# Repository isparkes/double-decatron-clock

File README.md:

# Two Decatron Clock

KiCad hardware for a two-tube Decatron (dekatron) clock driven by a Wemos D1 Mini
(ESP8266), plus the tube carrier board and an early, unfinished firmware sketch.

The board generates its own ~400 V anode supply and ~110 V guide rail, drives two
dual-guide A101 dekatrons, and reads each tube's index mark back through an
optocoupler.

> ⚠️ **This board carries ~400 V DC.** The HV multiplier and the tube connectors are
> live whenever `HV_EN` is asserted, and the reservoir capacitors stay charged after
> power-off. Treat the whole top side as hot.

## Status

The hardware is finished and was fabricated (`adfed9c Fab`, Oct 2021), with small
fixes through to Dec 2023.

**The standalone firmware was never finished.** The sketch under `Software/` stops
at version 0.1: it brings up Wi-Fi, NTP, the DS1307 and the full web config UI, and
it can step each tube, but there is no timer ISR and nothing ever renders the
prepared `displayHours` / `displayMins` / `displaySecs` values onto the tubes. The
only stepping that happens is the manual, button-driven index hunt in `setup()`.
Its pin map in `Software/ClockDefs.h` also predates commit `835bd50` ("Rearrange
outputs so that IDX work correctly") and **does not match the board as fabricated** —
see the pin table below for the as-built mapping.

Instead of being finished as a standalone clock, the board was repurposed as the
**dual-Decatron seconds display add-on for the ENIAC nixie clock**. The firmware it
actually runs lives in the separate `eniac-firmware` repository, as
`EniacDecatron` — an ESP8266 slave that receives a 5-byte framed packet
(`0xAA`, hours, minutes, seconds, control) once per second over UART from the ENIAC
ESP32 master, homes both tubes against their index marks, and drives tube 1 as a
rotating seconds hand. `DecatronTest` in the same repository emulates the master for
bench testing.

Because the add-on takes its time over the serial link, the on-board DS1307, the
Wi-Fi stack and the web UI are all unused in that role. Note that the front-panel
connector's `BTN1` pin lands on the Wemos `RX` pin — in ENIAC use that pin carries
serial data from the master instead of a button.

`Software/DecatronClock/` is a newer attempt at the standalone case: a PlatformIO
project built on the EniacDecatron tube handling, with the UART link to the ENIAC
master replaced by a local time source (NTP → DS1307 → serial), showing hours on one
tube and minutes on the other. It is a working skeleton rather than a finished
clock — see [`Software/DecatronClock/README.md`](Software/DecatronClock/README.md).

## Repository layout

| Path | Description |
|---|---|
| `Hardware/` | Main board: Wemos D1 Mini carrier, HV supply, guide drivers, index sensing, RTC. KiCad project `WemosDecatron`. |
| `Hardware/A101base/` | Dual A101 tube carrier board. KiCad project `A101base`. |
| `Hardware/WemosDecatronExternal.sch` | Off-board front-panel sheet (button + PIR). Legacy KiCad 4 schematic, documentation only — no PCB, and it still shows an 8-way front connector where the main board now has a 5-way one. Rendered as `WemosDecatronExternal.svg`. |
| `Hardware/Recovered.pretty/` | Recovered footprints. |
| `LICENSE` | Attribution / non-commercial terms covering both the hardware and the firmware. |
| `Software/DecatronClock/` | Standalone clock firmware: hours on one tube, minutes on the other. PlatformIO, ESP8266. |
| `Software/*.ino`, `Software/*.cpp` | Abandoned v0.1 standalone firmware (Arduino IDE, ESP8266). Reference only. |

Gerbers and drill files for `A101base` are generated into `A101base/CAM/`, which is
git-ignored along with the KiCad `*-backups` directories.

## Hardware

### Main board — `Hardware/WemosDecatron`

65 × 75 mm, two layers, through-hole throughout, four M3 mounting holes.
Title block: *"Wemos D1 Two Decatron clock"*, Rev 002, Glowtime Ltd.

**Power in.** DC enters on `J3`, through reverse-polarity diode `D1` (UF4007) to
`VIN`, then an L7805 (`U3`) produces the 5 V `VCC` that feeds the Wemos.

**High voltage.** An MC34063A (`U4`) switches an IRF640 (`Q2`) through a 100 µH
inductor (`L1`), with `R1` (0R18 2 W) as the current sense. `D3` rectifies the
switch node into the ~150 V rail (`C13` reservoir). A three-stage
Cockcroft–Walton multiplier (`C1`–`C4`, `D4`–`D7`) hanging off the same switch node
produces the ~400 V anode rail. Feedback is set by `R4`/`R5`/`RV1`; `RV1` (1 k) trims
the output.

**HV enable.** `Q5` (2N7000), driven from `HV_EN`, switches the feedback divider so
the firmware can turn the generator off for blanking. Solder jumper `JP1` ties
`HV_EN` to `VCC` for bench bring-up without a microcontroller.

**Tube drive.** Each tube's anode is fed from the 400 V rail through a 470 k series
resistor (`R16` for tube 1, `R2` for tube 2). `R12` (33 k) drops the 150 V rail to
the ~110 V guide rail. Each guide sits at 110 V through a 470 k pull-up
(`R9`/`R11` for tube 1, `R18`/`R20` for tube 2) and is pulled to ground by an MPSA42
(`Q3`/`Q4` and `Q6`/`Q7`). The common cathode return `RTN` is decoupled by `C5` and
`C15` (added in `021e908`, "Add RTN smoothing caps").

**Index sensing.** The index cathode of each tube drives the LED of an EL817
optocoupler (`U1`, `U6`) against `RTN`; the transistor side pulls `IDX1`/`IDX2` down
against a 3V3 pull-up (`R15`, `R21`). The index signal is therefore **active low** and
fully isolated from the HV side.

**Timekeeping.** A DS1307 (`U5`) with crystal `Y1` and CR1220 backup cell `BT1`,
on the Wemos I²C pins, also brought out on the 4-way header `J5` (added in
`6aa0615`).

**Test pads.** `W1` 5V, `W2`/`W3` GND, `W4` the 150 V rail (silk reads 170 V),
`W5` 110 V, `W6` `RTN` (silk reads 55 V), `W7` 400 V, `W8` `VIN`.

### Tube carrier — `Hardware/A101base`

71 × 39 mm, two layers. Two A101 dekatron footprints (`D1`, `D2`), each with its own
5-way header, plus two M3 mounting holes. Title block: *"A101 tube mount"*, Rev 001.

Per tube it commons K0 and K2–K9 to the return pin and brings out the anode, the
**K1 index cathode**, and the two guides. Note that the index is taken from K1, not
K0.

## Connectors

### Main board

| Ref | Pins | Function | Pinout |
|---|---|---|---|
| `J1` | 5 | Decatron 1 | 1 `400V_1` · 2 `IDX_IN1` · 3 `RTN` · 4 `G2_1` · 5 `G1_1` |
| `J4` | 5 | Decatron 2 | 1 `400V_2` · 2 `IDX_IN2` · 3 `RTN` · 4 `G2_2` · 5 `G1_2` |
| `J2` | 5 | Front panel | 1 `GND` · 2 `BTN1` · 3 `PIR` · 4 `VCC` (5 V) · 5 `3V3` |
| `J3` | 2 | DC input | 1 `GND` · 2 `V+` |
| `J5` | 4 | I²C | 1 `SDA` · 2 `SCL` · 3 `3V3` · 4 `GND` |

### A101 carrier (`J1`, `J2`)

| Pin | Signal |
|---|---|
| 1 | Anode |
| 2 | K1 (index) |
| 3 | Common return (K0, K2–K9) |
| 4 | G1 |
| 5 | G2 |

**Guide ordering:** with a straight 1:1 cable, main-board pin 4 (`G2_n`) lands on the
carrier's `G1` and pin 5 (`G1_n`) on `G2`, so the guide pair is swapped and the glow
rotates the opposite way round. The firmware compensates in its phase sequence —
`EniacDecatron` steps the glow *forward* by *decrementing* the phase. Keep this in
mind before "fixing" either end.

## ESP8266 pin map (as fabricated)

Taken from the PCB netlist, not from `Software/ClockDefs.h`.

`EniacDecatron` and `Software/DecatronClock` use the same set of pins, but their
`defs.h` deliberately maps them differently: firmware "Decatron 1" is the board's
`J4`/Decatron2 connector, and G1/G2 are swapped within each tube, to compensate for
the pin 4/5 ordering described above. That mapping is empirical and known to work —
do not reconcile it with this table without a tube on the bench. (The
`EniacDecatron/SPECIFICATION.md` pin table is itself out of date with respect to its
own `defs.h`.)

| Signal | D1 Mini pin | Direction | Notes |
|---|---|---|---|
| `G1_1` | D4 | out | Tube 1 guide 1 |
| `G2_1` | D3 | out | Tube 1 guide 2 |
| `IDX1` | D0 | in | Tube 1 index, active low (opto) |
| `G1_2` | D6 | out | Tube 2 guide 1 |
| `G2_2` | D5 | out | Tube 2 guide 2 |
| `IDX2` | D7 | in | Tube 2 index, active low (opto) |
| `HV_EN` | D8 | out | HV generator enable, active high |
| `SDA` | D2 | — | DS1307 / `J5` |
| `SCL` | D1 | — | DS1307 / `J5` |
| `PIR` | A0 | in | Front panel `J2` |
| `BTN1` | RX | in | Front panel `J2`; also the UART RX used by `EniacDecatron` |

## Working with the files

The schematics are KiCad 6 format (`version 20211123`); `WemosDecatron.kicad_pcb` has
since been re-saved by a newer KiCad and will want to migrate the schematic on open.
The legacy KiCad 5 files (`.sch`, `.net`, `.lib`, `.cmp`, `.mod`) are kept alongside
for reference and are not maintained.

Footprints come from a global `NixieClockMaster` library that is **not** part of this
repository; the local `fp-lib-table` is empty, so that library must be configured
globally in KiCad for the boards to open with footprints resolved.
`Hardware/WemosDecatron.csv` is a BOM export, generated before the latest revisions —
check it against the schematic before ordering.

### Firmware

For a standalone clock, build `Software/DecatronClock` with PlatformIO
(`pio run -t upload`, env `d1_mini`). No external library dependencies.

For the add-on role, build `EniacDecatron` from the `eniac-firmware` repository, also
with PlatformIO (env `d1_mini`, 160 MHz, 115200 baud).

The loose sketch at the top of `Software/` is an Arduino IDE project (board:
*LOLIN(WeMos) D1 R2 & mini*, 4 MB flash / 2 MB FS). It depends on Time (Margolis
1.5.0) and WiFiManager (tzapu 0.14.0). It is kept for reference only — it is
incomplete and its pin map is out of date.

## License

Attribution-NonCommercial — see [`LICENSE`](LICENSE). Free to use, modify and build
for personal, educational and hobbyist purposes, with credit; commercial use,
including selling boards or kits, needs a separate written license. The same terms
as the `eniac-firmware` repository.

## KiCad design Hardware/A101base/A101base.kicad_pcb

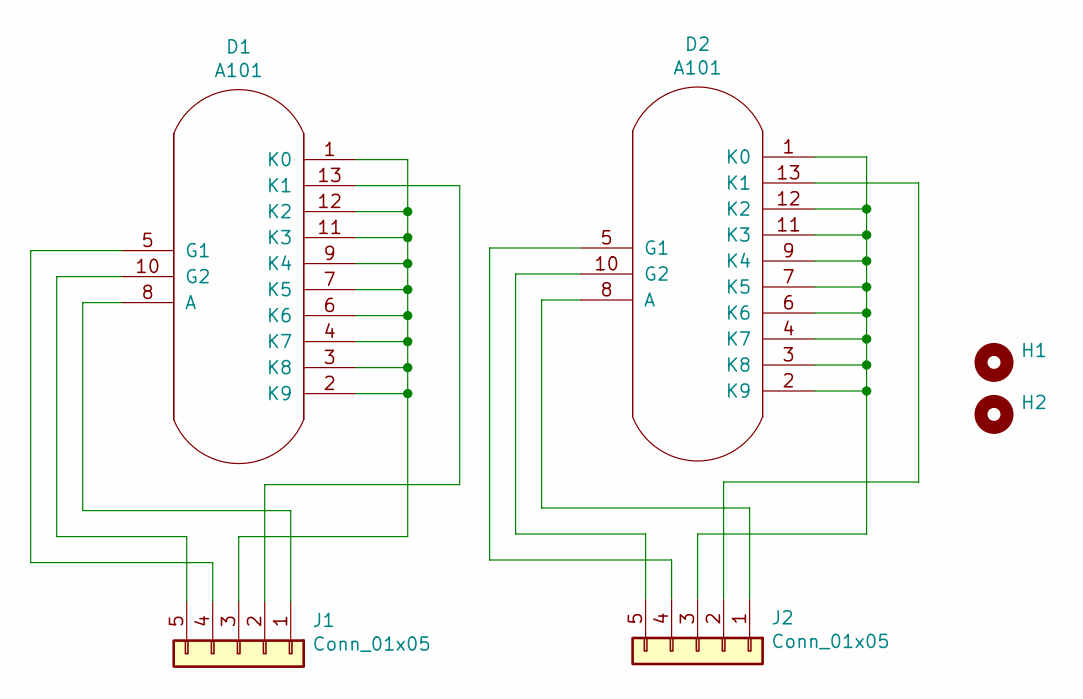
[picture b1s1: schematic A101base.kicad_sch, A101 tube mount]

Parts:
D1, D2: A101; A101-TopView
H1, H2: MountingHole; MountingHole_3.2mm_M3
J1, J2: Conn_01x05; Header_MA05-1

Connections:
unnamed: D1.1 (K0), D1.2 (K9), D1.3 (K8), D1.4 (K7), D1.6 (K6), D1.7 (K5), D1.9 (K4), D1.11 (K3), D1.12 (K2), J1.3
unnamed: D1.5 (G1), J1.4
unnamed: D1.8 (A), J1.1
unnamed: D1.10 (G2), J1.5
unnamed: D1.13 (K1), J1.2
unnamed: D2.1 (K0), D2.2 (K9), D2.3 (K8), D2.4 (K7), D2.6 (K6), D2.7 (K5), D2.9 (K4), D2.11 (K3), D2.12 (K2), J2.3
unnamed: D2.5 (G1), J2.4
unnamed: D2.8 (A), J2.1
unnamed: D2.10 (G2), J2.5
unnamed: D2.13 (K1), J2.2

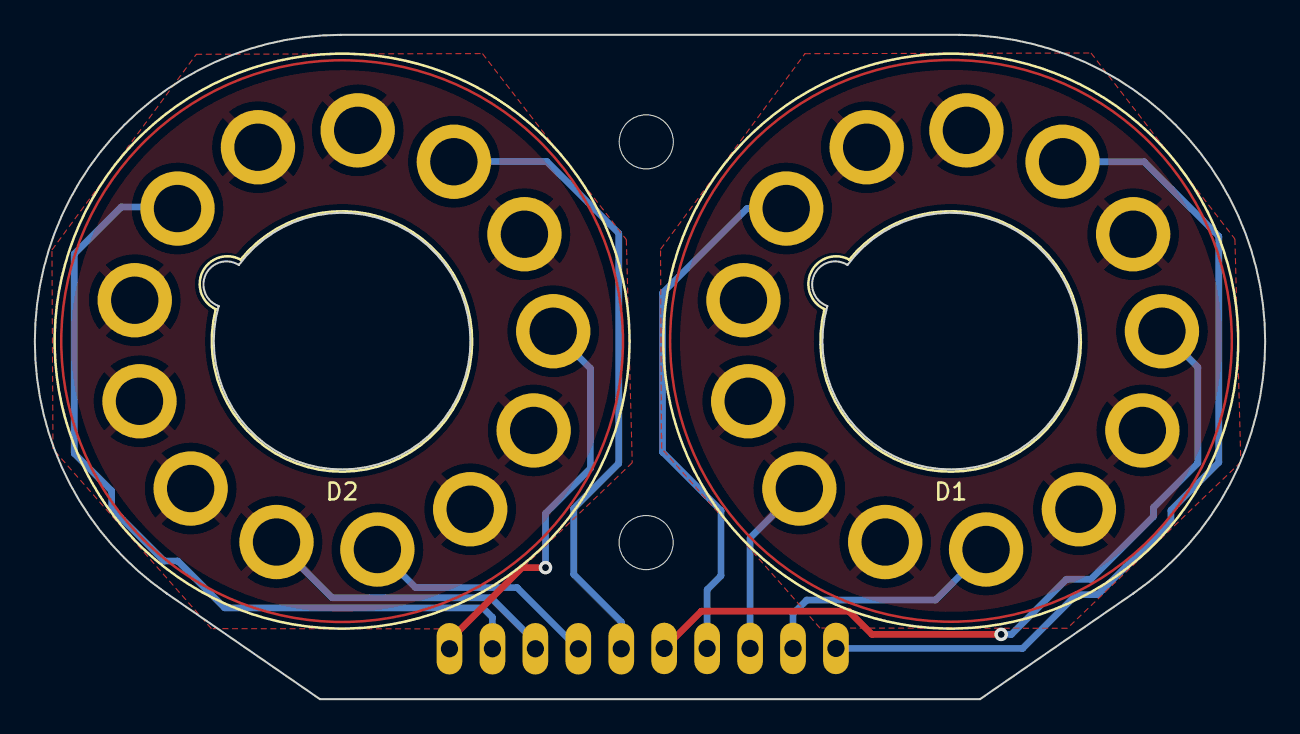
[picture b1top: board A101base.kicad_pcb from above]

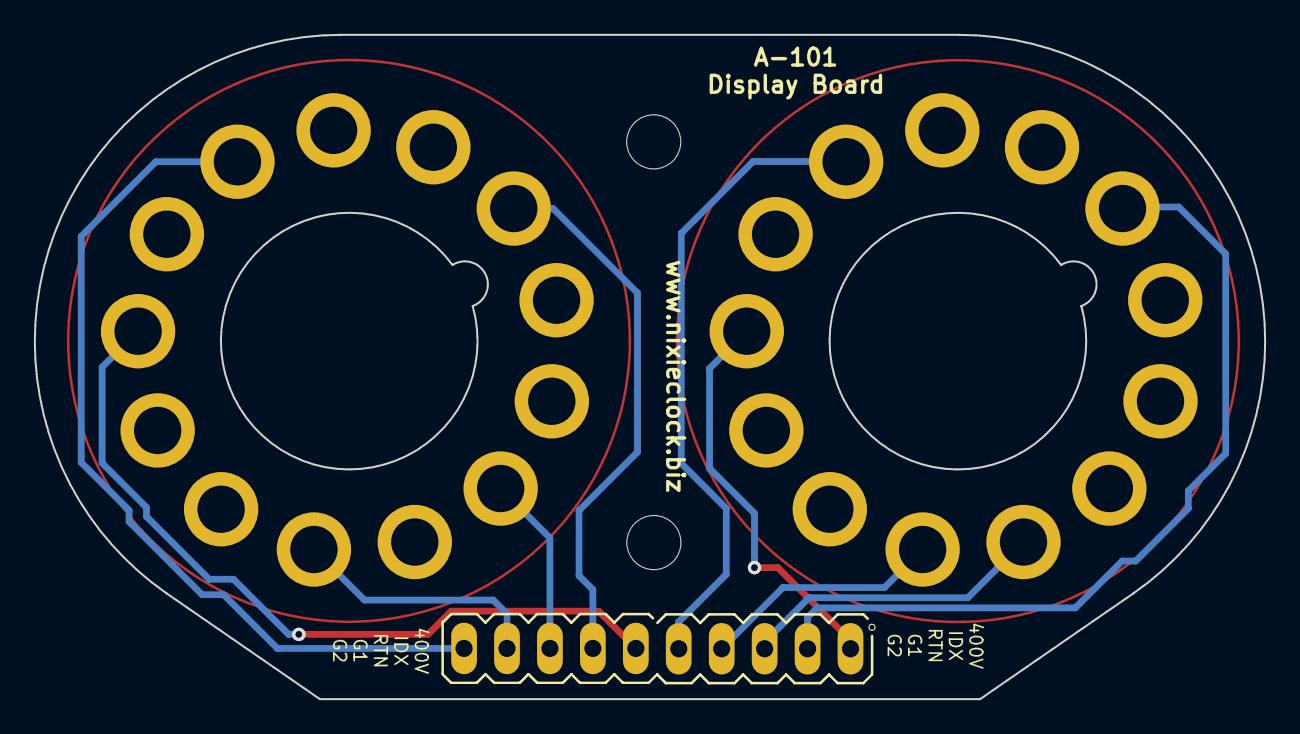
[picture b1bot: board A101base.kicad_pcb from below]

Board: 2 copper layers, 72.8 x 39.3 mm, 6 parts (2 on the bottom side), 10 nets.

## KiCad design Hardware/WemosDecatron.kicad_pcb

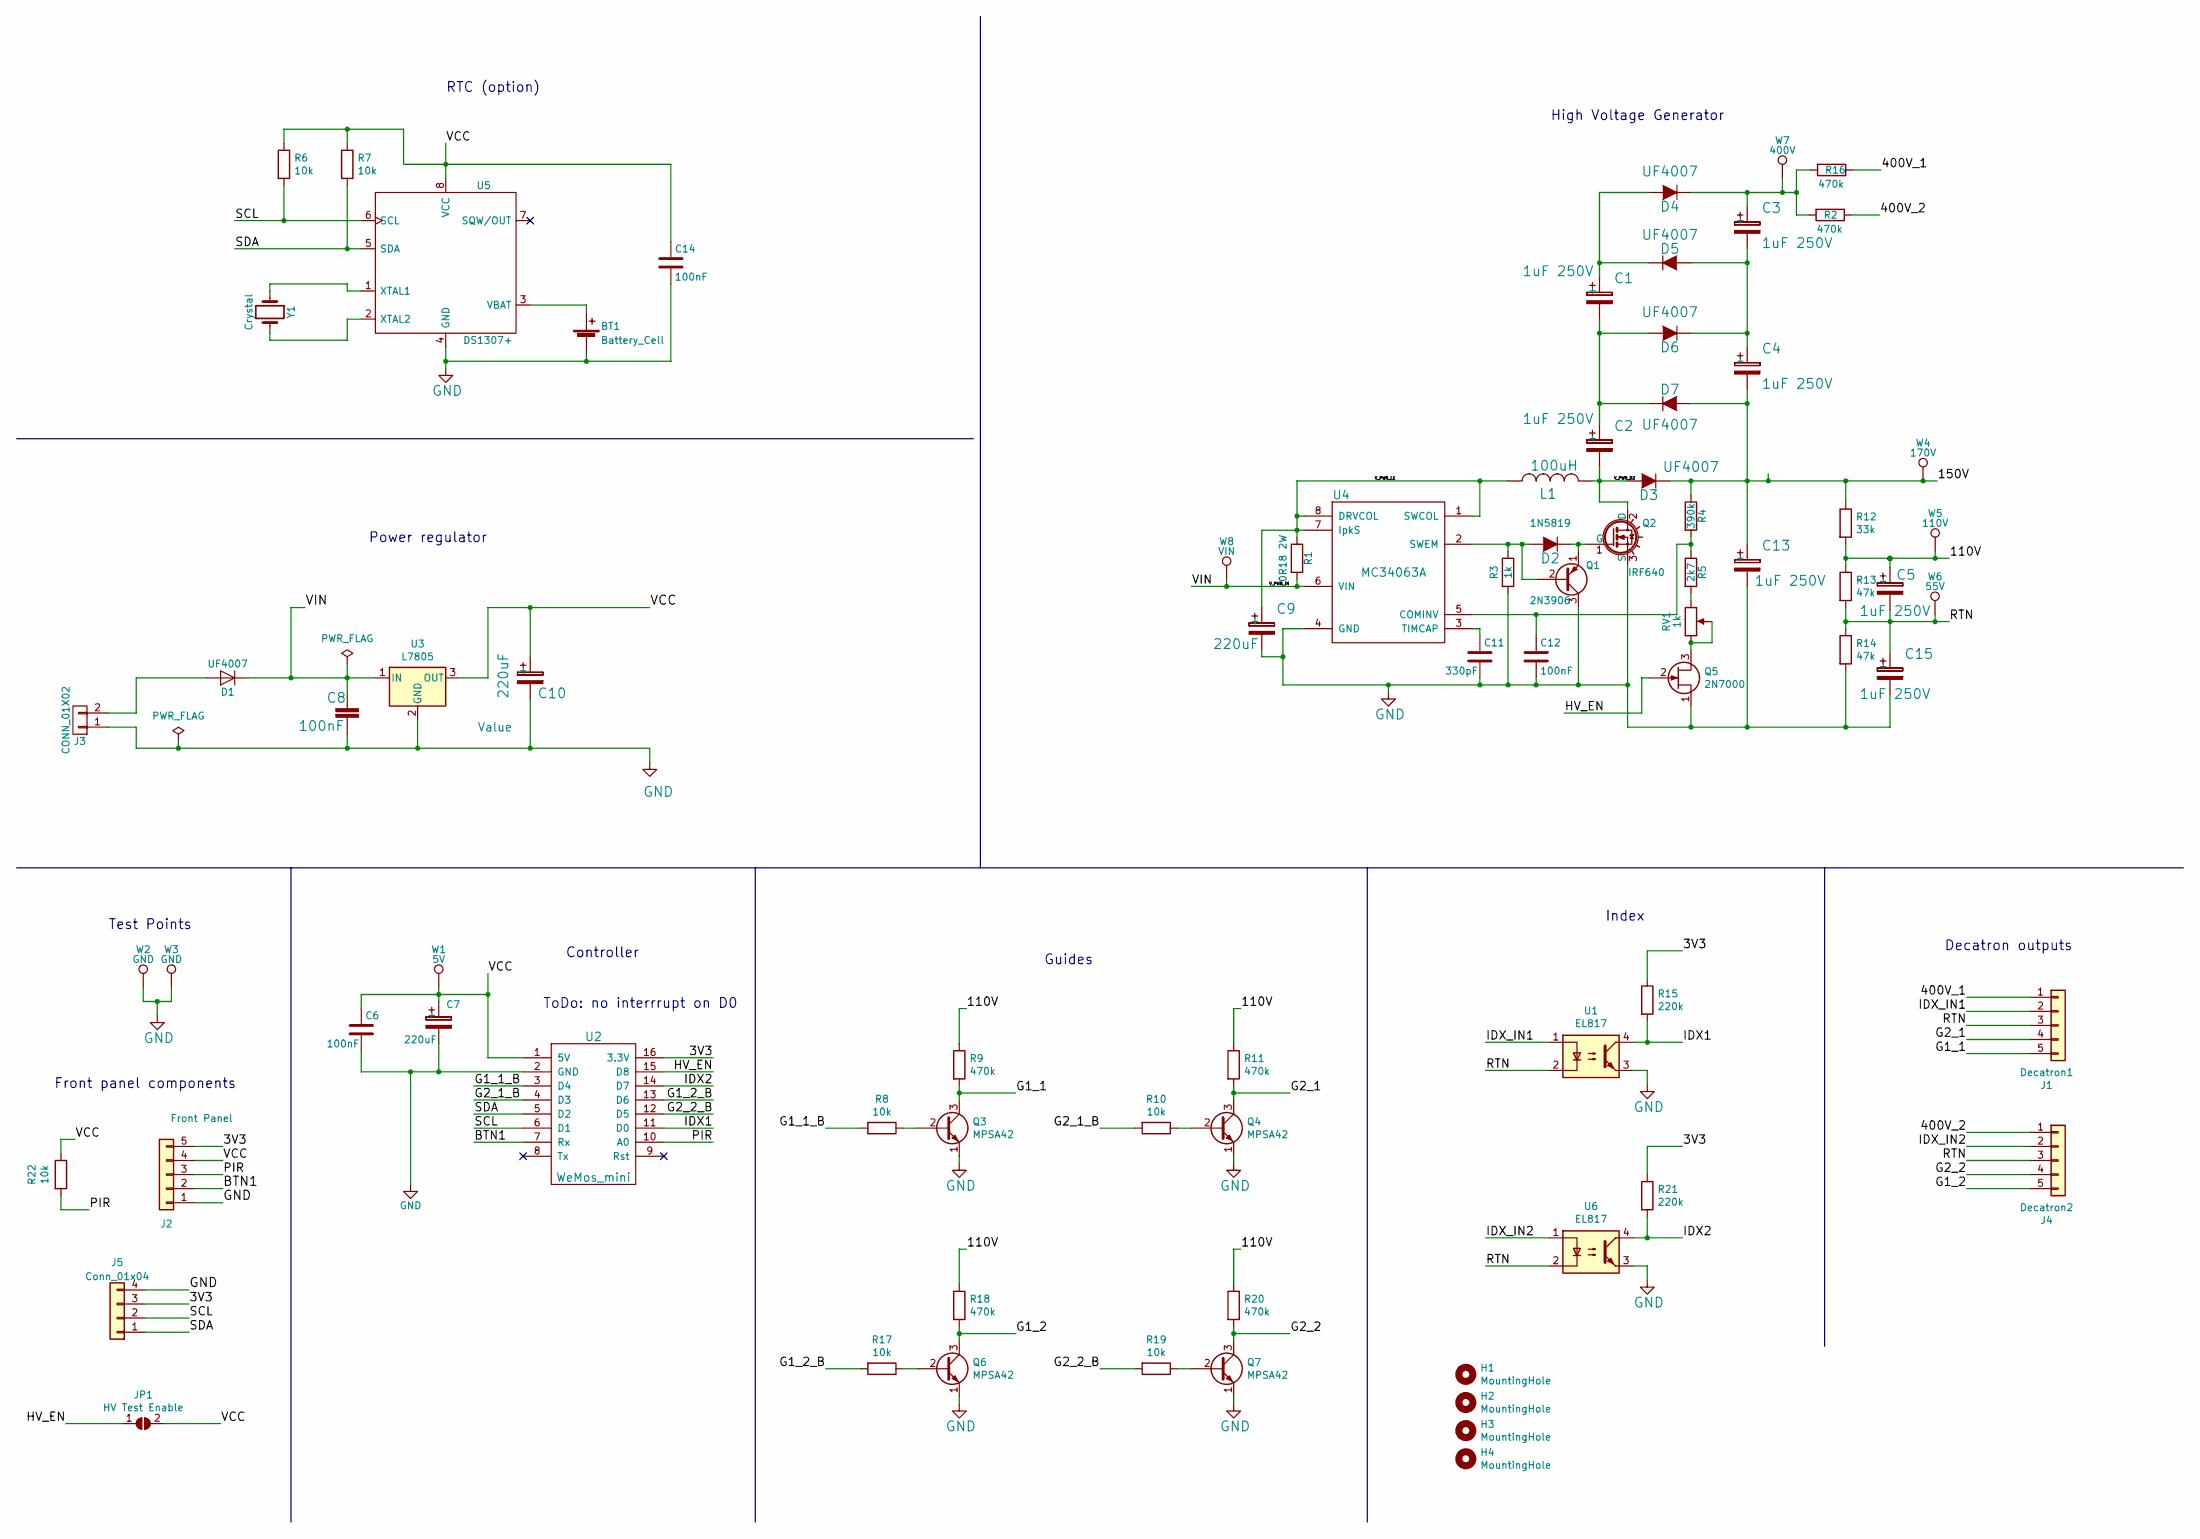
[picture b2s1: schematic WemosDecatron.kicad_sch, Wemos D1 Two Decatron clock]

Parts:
BT1: Battery_Cell; CR1220-CoinCell
C1, C2, C3, C4, C5, C13, C15: 1uF 250V; CP_Radial_D5.0mm_P2.00mm
C6, C8, C12, C14: 100nF; C025-024X044
C7, C9, C10: 220uF; C_Radial_D6.3_L11.2_P2.5
C11: 330pF; C025-024X044
D1: UF4007; Diode_DO-41_SOD81_Vertical_AnodeUp
D2: 1N5819; Diode_DO-41_SOD81_Vertical_AnodeUp
D3, D4, D5, D6, D7: UF4007; Diode_DO-41_1N4001
H1, H2, H3, H4: MountingHole; MountingHole_3.2mm_M3
J1: Decatron1; Header_MA05-1
J2: Front Panel; Header_MA05-1
J3: CONN_01X02; Header_MA02-1
J4: Decatron2; Header_MA05-1
J5: Conn_01x04; Header_MA04-1
JP1: HV Test Enable; SOLDER-JUMPER
L1: 100uH; Inductor-100mH
Q1: 2N3906; TO-92_inline_2N3906
Q2: IRF640; TO-220-3_H
Q3, Q4, Q6, Q7: MPSA42; TO-92_inline_MPSA42
Q5: 2N7000; TO-92_inline_2N7000
R1: 0R18 2W; R_2W
R2, R9, R11, R16, R18, R20: 470k; R-0207_2V
R3: 1k; R-0207_2V
R4: 390k; R-0207_2V
R5: 2k7; R-0207_2V
R6, R7, R22: 10k; R-0207_2V
R8, R10, R17, R19: 10k; R_Axial_DIN0204_L3.6mm_D1.6mm_P7.62mm_Horizontal
R12: 33k; R-0207_2V
R13, R14: 47k; R-0207_2V
R15, R21: 220k; R-0207_2V
RV1: 1k; Potentiometer_Trimmer_Bourns_3296X
U1, U6: EL817; optocoupler-DIL04
U2: WeMos_mini; WeMos_D1_mini_board_flipped
U3: L7805; TO-220-3_H
U4: MC34063A; MC34063_DIL8
U5: DS1307+; DS1307_DIL8
W1: 5V; TESTPAD_P1-13
W2, W3: GND; TESTPAD_P1-13
W4: 170V; TESTPAD_P1-13
W5: 110V; TESTPAD_P1-13
W6: 55V; TESTPAD_P1-13
W7: 400V; TESTPAD_P1-13
W8: VIN; TESTPAD_P1-13
Y1: Crystal; Crystal_DS10_d1.0mm_l4.3mm_Vertical

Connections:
/3V3: J2.5, J5.3, R15.1, R21.1, U2.16 (3.3V)
/110V: C5.1, R9.1, R11.1, R12.2, R13.1, R18.1, R20.1, W5.1
/150V: C4.2, C13.1, D3.1 (K), D7.2 (A), R4.1, R12.1, W4.1
/400V_1: J1.1, R16.1
/400V_2: J4.1, R2.1
/BTN1: J2.2, U2.7 (Rx)
/G1_1: J1.5, Q3.3 (C), R9.2
/G1_1_B: R8.2, U2.3 (D4)
/G1_2: J4.5, Q6.3 (C), R18.2
/G1_2_B: R17.2, U2.13 (D6)
/G2_1: J1.4, Q4.3 (C), R11.2
/G2_1_B: R10.2, U2.4 (D3)
/G2_2: J4.4, Q7.3 (C), R20.2
/G2_2_B: R19.2, U2.12 (D5)
/HV_EN: JP1.1 (A), Q5.2 (G), U2.15 (D8)
/IDX1: R15.2, U1.4, U2.11 (D0)
/IDX2: R21.2, U2.14 (D7), U6.4
/IDX_IN1: J1.2, U1.1
/IDX_IN2: J4.2, U6.1
/PIR: J2.3, R22.2, U2.10 (A0)
/RTN: C5.2, C15.1, J1.3, J4.3, R13.2, R14.1, U1.2, U6.2, W6.1
/SCL: J5.2, R6.2, U2.6 (D1), U5.6 (SCL)
/SDA: J5.1, R7.2, U2.5 (D2), U5.5 (SDA)
/VCC: C6.1, C7.1, C10.1, C14.1, J2.4, JP1.2 (B), R6.1, R7.1, R22.1, U2.1 (5V), U3.3 (OUT), U5.8 (VCC), W1.1
/VIN: C8.2, D1.1 (K), R1.2, U3.1 (IN), U4.6 (VIN), W8.1
/V_PWR_D2: C2.2, D3.2 (A), L1.2, Q2.2 (D)
/V_PWR_L1: C9.1, L1.1, R1.1, U4.1 (SWCOL), U4.7 (IpkS), U4.8 (DRVCOL)
GND: BT1.2 (-), C6.2, C7.2, C8.1, C9.2, C10.2, C11.2, C12.2, C13.2, C14.2, C15.2, J2.1, J3.1, J5.4, Q1.3 (C), Q2.3 (S), Q3.1 (E), Q4.1 (E), Q5.1 (S), Q6.1 (E), Q7.1 (E), R3.2, R14.2, U1.3, U2.2 (GND), U3.2 (GND), U4.4 (GND), U5.4 (GND), U6.3, W2.1, W3.1
unnamed: BT1.1 (+), U5.3 (VBAT)
unnamed: C1.1, D4.2 (A), D5.1 (K)
unnamed: C1.2, C2.1, D6.2 (A), D7.1 (K)
unnamed: C3.1, D4.1 (K), R2.2, R16.2, W7.1
unnamed: C3.2, C4.1, D5.2 (A), D6.1 (K)
unnamed: C11.1, U4.3 (TIMCAP)
unnamed: C12.1, R4.2, R5.1, U4.5 (COMINV)
unnamed: D1.2 (A), J3.2
unnamed: D2.1 (K), Q1.1 (E), Q2.1 (G)
unnamed: D2.2 (A), Q1.2 (B), R3.1, U4.2 (SWEM)
unnamed: Q3.2 (B), R8.1
unnamed: Q4.2 (B), R10.1
unnamed: Q5.3 (D), RV1.2, RV1.3
unnamed: Q6.2 (B), R17.1
unnamed: Q7.2 (B), R19.1
unnamed: R5.2, RV1.1
unnamed: U5.1 (XTAL1), Y1.1
unnamed: U5.2 (XTAL2), Y1.2

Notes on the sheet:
Decatron outputs
RTC (option)
Power regulator
Front panel components
High Voltage Generator
Test Points
Controller
Guides
ToDo: no interrrupt on D0
Index

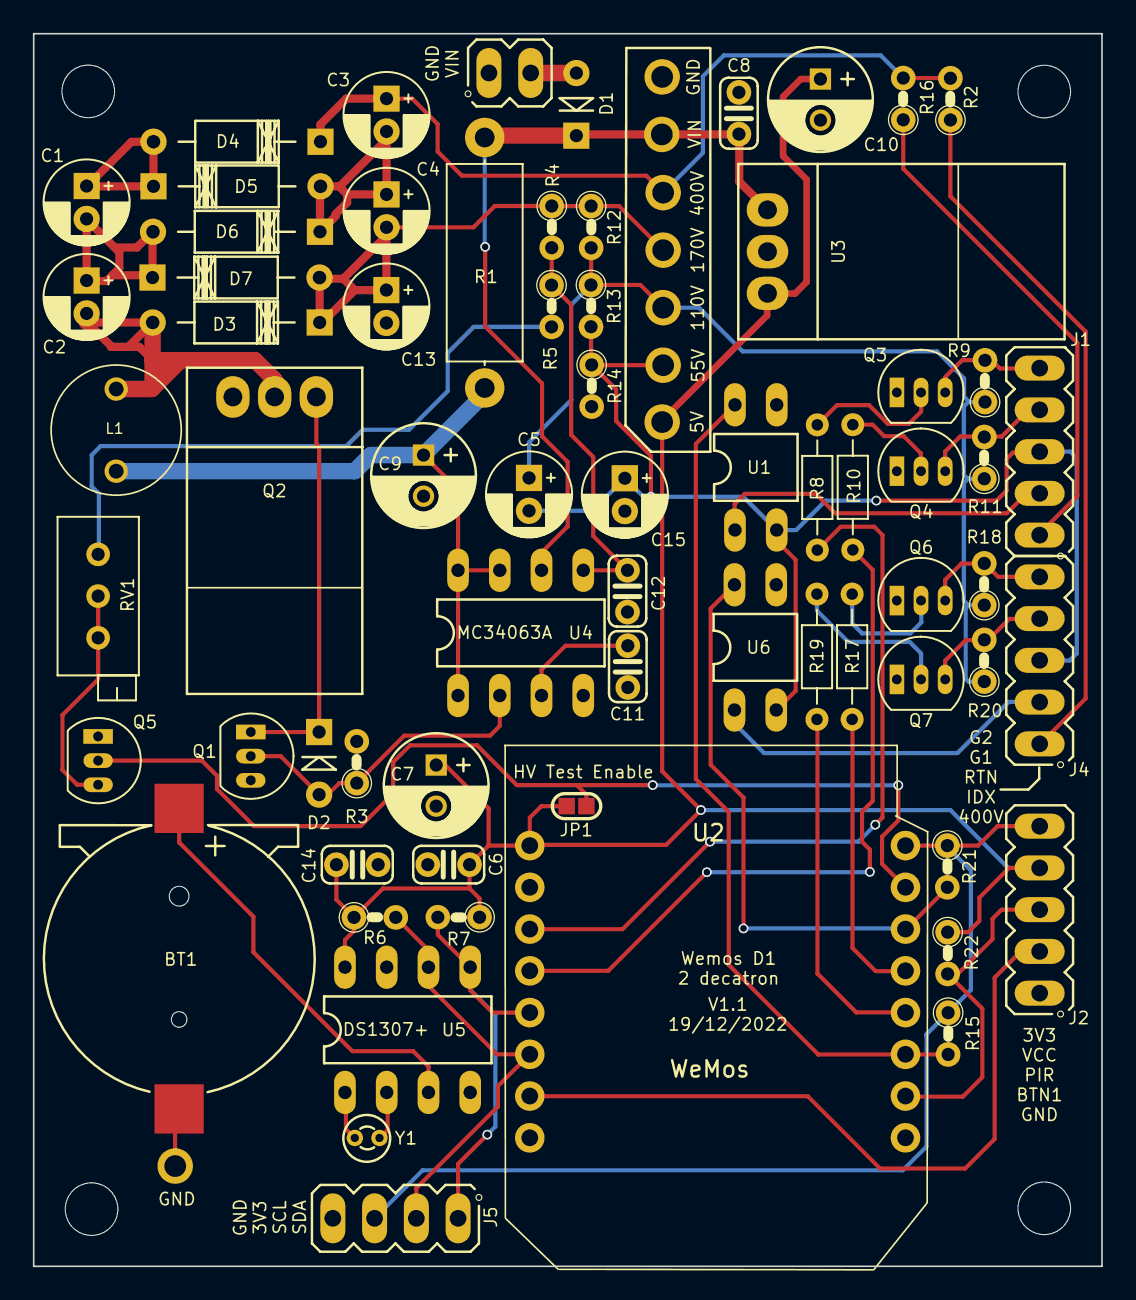
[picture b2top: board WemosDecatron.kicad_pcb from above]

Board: 2 copper layers, 65.0 x 75.0 mm, 79 parts (0 on the bottom side), 46 nets.

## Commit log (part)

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2021-06-20 Update after test
2021-06-21 Firmware version 0.1
2021-08-13 Rearrange outputs so that IDX work correctly
2021-10-05 Add PIR pullup
2022-12-20 Add I2C header
2022-12-20 Dual A101 base
2023-05-29 ignore
2023-10-02 Correct mounting hole
2023-12-16 Add RTN smoothing caps
